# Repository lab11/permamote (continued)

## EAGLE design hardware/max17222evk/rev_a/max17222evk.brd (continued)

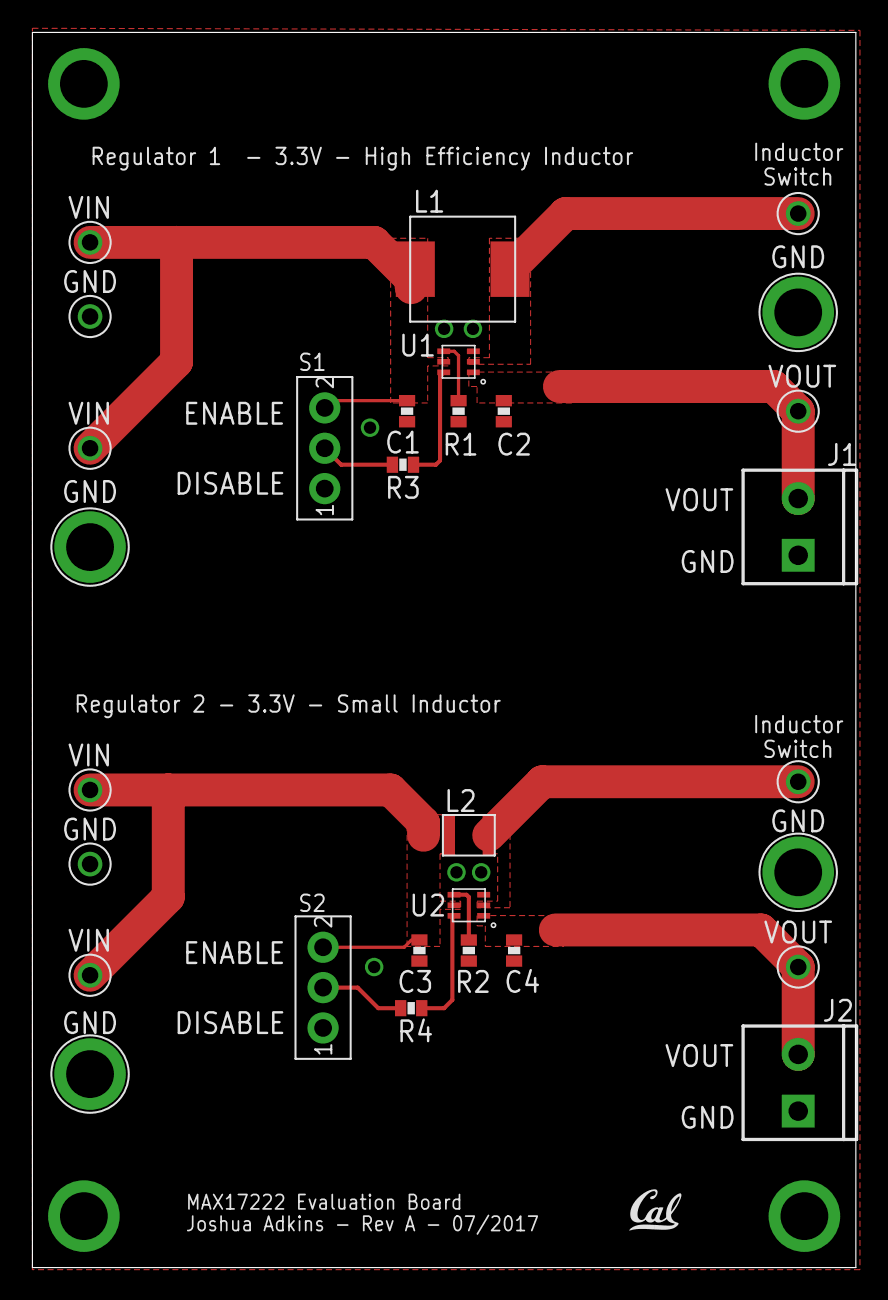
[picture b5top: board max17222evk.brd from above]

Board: 2 copper layers, 50.8 x 76.2 mm, 31 parts (0 on the bottom side), 13 nets.

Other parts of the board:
U$1: UCB_CAL_100MIL

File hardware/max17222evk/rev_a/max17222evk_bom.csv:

"Qty";"Value";"Device";"Package";"Parts";"Description";"DIGIKEY";"MANUFACTURER";"MANUFACTURER_PN";"NEWARK";
"2";"";"M023.5MM";"SCREWTERMINAL-3.5MM-2";"J1, J2";"Header 2";"277-1721-ND";"";"";"";
"4";"10uF";"CAPACITOR0603_CAP";"0603_CAP";"C1, C2, C3, C4";"SMD Capacitor";"490-3896-2-ND";"";"";"";
"1";"1uH";"INDUCTORDFE322512C";"DFE322512C";"L2";"A very specific inductor";"490-10590-1-ND";"";"";"";
"1";"1uH";"INDUCTORIHL2525CZ";"IHL-2525CZ";"L1";"A very specific inductor";"541-2562-1-ND";"";"";"";
"2";"33M";"RESISTOR0603_RES";"0603-RES";"R3, R4";"Resistor";"HMC0603JT33M0CT-ND";"";"";"";
"2";"80.6k";"RESISTOR0603_RES";"0603-RES";"R1, R2";"Resistor";"311-80.6KHRCT-ND";"";"";"";
"2";"MAX17222";"MAX17222";"UDFN-6-MAXIM";"U1, U2";"Very high efficiency, very low power boost converter suitable for EH applications";"MAX17222ELT+TCT-ND";"MAXIM INTEGRATED";"MAX17222ELT+T";"";
"10";"TEST_POINT_0.040IN";"TEST_POINT_0.040IN";"TESTPOINT_0.040IN";"TP3, TP4, TP5, TP6, TP7, TP8, TP9, TP10, TP13, TP14";"0.040in Test Point";"5001K-ND";"";"";"";
"4";"TEST_POINT_0.112IN";"TEST_POINT_0.112IN";"TESTPOINT_0.112IN";"TP1, TP2, TP11, TP12";"Solder terminal, turreted";"36-1519-2-ND";"";"";"40F6015";
"2";"TE_SSA12/SPDT";"TE_SSA12/SPDT";"TE_SSA12/SPDT";"S1, S2";"SWITCH SLIDE SPDT 2POS SSA SER";"450-1602-ND";"";"";"";

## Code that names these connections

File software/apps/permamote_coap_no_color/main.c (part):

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  NRF_LOG_INFO("Sensed voltage: vbat*100: %d, vsol*100: %d, vsec*100: %d", (int32_t)(vbat*100), (int32_t)(vsol*100), (int32_t)(vsec*100));

  // sense vbat_ok
  bool vbat_ok = nrf_gpio_pin_read(VBAT_OK);
  packet.data = (uint8_t*)&vbat_ok;
  packet.data_len = sizeof(vbat_ok);
  permamote_coap_send(&m_peer_address, "vbat_ok", false, &packet);
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}

static void pir_backoff_callback() {
  nrf_drv_gpiote_in_event_enable(PIR_OUT, 1);
}

static void pir_interrupt_callback(nrf_drv_gpiote_pin_t pin, nrf_gpiote_polarity_t action) {
  nrf_drv_gpiote_in_event_disable(PIR_OUT);
  uint32_t err_code = app_timer_start(pir_backoff, PIR_BACKOFF_PERIOD, NULL);
  APP_ERROR_CHECK(err_code);

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  nrf_gpio_cfg_output(TCS34725_EN);
  nrf_gpio_cfg_output(MS5637_EN);
  nrf_gpio_cfg_output(SI7021_EN);
  nrf_gpio_cfg_output(PIR_EN);
  nrf_gpio_pin_clear(MAX44009_EN);
  nrf_gpio_pin_clear(PIR_EN);
  nrf_gpio_pin_set(TCS34725_EN);
  nrf_gpio_pin_set(MS5637_EN);
  nrf_gpio_pin_set(SI7021_EN);
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  }
  nrf_drv_gpiote_in_config_t pir_gpio_config = GPIOTE_CONFIG_IN_SENSE_LOTOHI(1);
  pir_gpio_config.pull = NRF_GPIO_PIN_PULLDOWN;
  nrf_drv_gpiote_in_init(PIR_OUT, &pir_gpio_config, pir_interrupt_callback);
  nrf_drv_gpiote_in_event_enable(PIR_OUT, 1);

  // setup vbat sense
  nrf_gpio_cfg_input(VBAT_OK, NRF_GPIO_PIN_NOPULL);

  ab1815_init(&spi_instance);
  ab1815_control_t ab1815_config;
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
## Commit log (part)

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2018-07-19 coap is a better term
2018-07-19 coap app read id from flash
2018-07-20 add motion parsing
2018-07-23 add part marker to U12
2018-07-24 add PIR to coap app
2018-07-24 add parsing for temp/pressure
2018-07-24 Fixup si7021 driver to use twi mngr
    Add test app to print temp/humidity
2018-07-25 add humidity parsing
2018-07-25 Move jtag connector to back
2018-07-25 Add app support for humidity and voltage sensing
    fix humidity and light driver bugs
2018-07-25 update voltage names
2018-07-31 start driver for tcs34725
2018-08-02 add reset to parser
2018-08-02 better handling of corner cases, max44009
2018-08-02 Fill out tcs driver
2018-08-07 Add driver and test app for RTC
    test app sets rtc time, prints out read time every 5 seconds
2018-08-08 Add function to convert unix to ab1815 time format
2018-08-27 Add new pin defs for revb
2018-08-28 Attempt to add ntp+rtc support to permamote
    SPI manager sucks and hangs - need to use drv interface
2018-08-28 start of test app for tcs
2018-08-29 TCS driver and test working
2018-09-05 Switch to new NRFX base build system
    Add permamote board config files
    All test apps working on new build system - print over rtt
2018-09-05 Redesign case
    unibody design with clips to hold solar panel above board
2018-09-10 fix led count
2018-09-10 Use permamote packet send layer
2018-09-11 add light color measurements to main app
2018-09-11 update README to be more informative
2018-09-14 add debug print/sending for buffer allocation
2018-09-24 add topic to parsed message
2018-10-03 use channel 25 for less interference
2018-10-04 add support for rtc alarm
    Use alarm in coap app to periodically update rtc with ntp
2018-10-04 start state machine
2018-10-04 fix up ntp error handling - handle timeout
    fix rtc alarm repeat time setting
2018-10-05 add simple software watchdog
2018-10-06 out for quotes
2018-10-08 Add rtc watchdog
    coap app now enables and tickles watchdog upon successful packet queue
    and if connected to network
2018-10-11 Move lighting control stuff to own repo
2018-10-28 add light sensing to periodic
2018-11-28 actually turn off PIR
    add intents for buffer
2018-12-05 parse vbat_ok
2018-12-08 Add autoranging of color sensor
    Autorange based on clear channel count, 4 settings.
    Also change method for calculating color temperature
2018-12-11 use dns to resolve coap/ntp addresses
2018-12-14 Update to new openthread libraries, nrf sdk 15.2.0
    Update coap app to only tickle watchdog periodically instead of every
    send.
2019-01-07 Add a background bootloader for thread dfu
    Add bootloader board files
2019-01-08 relax sensor modes
2019-01-10 Got DFU over thread working
    Currently need to manually follow steps for generating/merging
    bootloader settings as listed here: https://www.nordicsemi.com/DocLib/Content/SDK_Doc/Thread_SDK/v2-0-0/thread_example_dfu
    Need to play around with block sizes and polling intervals for faster
    DFU, but it works!
2019-01-12 Add connect and address resolve to state machine
2019-01-14 differentiate sensing periods
2019-01-16 deprecate color sensor
2019-01-24 start icount calibration script
2019-01-29 switch to yaml config
2019-02-04 Turn LED on in main
2019-02-07 start script to process
2019-02-08 clean up curve
2019-02-08 try 4 wire sensing, plot data
2019-02-12 clean up processing
2019-02-12 percent to capacity
2019-02-12 manually set to 0 current instead of high z
2019-02-13 add hyst lines
2019-02-16 Stored a variable in flash
2019-02-20 Continue testing with flash storage API
2019-02-21 More flash API work
2019-02-22 Refactor address resolution and NTP update
    Add several more states to handle NTP updates, polling frequency updates
2019-02-23 Fix double counted PIR events
    Check dns errors, wait until successful
2019-02-23 Change discovery to periodic loop
2019-02-25 fix rev number in sch
2019-02-26 More fstorage disappointment
2019-03-05 Refactor simulator into class
    Clean up simulator, switch to yaml config
2019-03-05 Recalibrating fstorage stuff to deal with the fact that NVMC can't write 2x to same addr
2019-03-07 Add tutorial
2019-03-07 Create new test app for flash variables, using FDS
2019-03-07 Perform first FDS write
2019-03-08 debugging info - undo a lot of this later
2019-03-08 correctly sign firwmare
2019-03-11 Update openthread libs for SNTP
2019-03-12 Create FDS write wrapper function, start work on FDS read wrapper function
2019-03-13 add weight to parse js
2019-03-13 add permamote scale code
2019-03-14 Create more FDS helper functions
2019-03-18 Fix url in config, logic in address resolution
2019-03-18 Start new header file
2019-03-22 Work on bootstrapping problem for flash variable names
2019-03-22 Refactoring to implement tag-struct strategy
2019-03-25 Add app-level timeout for DFU failure
    Also now check for updates every day (24 hours)
2019-03-30 remove public keys
2019-03-30 Use actual update server
2019-03-30 Better performance with different coap settings
    Still need to figure out why no retransmit on dfu side
2019-03-31 pull up nrf5x-base
2019-03-31 print out git version
2019-04-02 Only start coap tick timer when performing dfu
    Also disable monitor for hung dfu
2019-04-02 add version string packet on start
2019-04-02 this repo is almost always dirty
2019-04-02 print out git version on build
2019-04-03 continue work
2019-04-04 refactor flash variable init
2019-04-11 split flash storage functions by data type
2019-04-12 fix bugs with float storage and update; still have to fix bugs with string update
2019-04-23 Create separate branch for non-volatile parameter updates
2019-04-23 Continue testing string updates with flash storage
2019-04-24 update readme to fix broken links
2019-04-26 Fix broken readme link
2019-04-26 Store Device ID in last bit of flash
    Should fix #6
    Move bootloader back, page for Device ID
2019-04-29 include more reserved pages
2019-04-30 Clean up garbage files, keys
2019-04-30 Don't need bootloader for this example
    Fix naming conflict in nrf52832
2019-04-30 Clean up flash test
2019-04-30 move flash storage to common folder
2019-05-02 Use new flash storage lib to store ID
2019-05-03 ensure dfu does not overwrite app data
2019-05-03 add jitter to dfu update
2019-05-09 Reduce frequency of adc measurements
    Make interrupt-based measurements confirmable
2019-05-10 refactor state machine
2019-05-17 send discover on boot
2019-06-05 reduce light sensor sensitivity
2019-06-05 Was not preserving openthread flash pages
    Set reserved pages to 4, ensure DFU and FDS account for them
2019-07-07 Add watchdog back in because can't fix dfu bug
2019-07-07 don't stop coap timer tick
2019-07-08 at a minimum, sample light sensor every so often
2019-07-09 Commit rev d
    Only major change is moving button + led. Button was previously
    partially overlapping battery connection
2019-07-17 clean and orient design blocks
2019-07-17 Route signals on board - no airwires or major drc
    Need to add optional MSP430
2019-07-30 Don't need `make flash_first_dfu` anymore!
2019-07-31 Move to new nRF52x-base repo
    [nRF52x](https://github.com/lab11/nrf52x-base)
2019-09-14 fix missing nrf52x commit
2019-09-14 Update README for git lfs
2019-09-19 Start ADC test
    got down to 400uA for two channels
2019-09-20 ADC sampling works with PPI
    but draws considerable current
2019-10-02 bump nrf52x
2019-10-04 Update Permamote to periodically send thread info
2019-10-14 Use nanopb instead of protobuf-c
    Update nordic's use of nanopb and patch implementation
    Update permamote app to use protobuf
    Need to fix cloud infrastructure to support protobufs
    Need to figure out platform/version independent way of generating proto
    c code
2019-10-23 fix exti floating
2019-10-23 Fix exti in rev d
2019-10-24 Add decoupling cap for camera supply
2019-10-25 Better support for protobuf generation
2019-10-26 add my comments
2019-10-26 oops missed the LED
2019-10-30 Incorporate branden's suggestions
    Add power switch, need to layout
2019-11-02 Route power switch
2019-11-02 ran the script and requested quote
2019-11-04 Holes for 18mm holders
2019-11-07 Fix BOM errors for resistor + battery
2019-11-07 flatten protobuf structure
2019-11-16 add proto files for testing
2019-11-16 rename to match old names of fields
2019-11-18 Benchmark CLA/CS measurements
2019-11-19 made revisions from schematic review
2019-11-20 added sd card
2019-11-26 Implement MCLK and some of SPIS
2019-11-26 Get 8MHz clock working
2019-11-27 freaking idiot
2019-11-28 rebuffer SPI for continuous
2019-12-01 Implement blocking image capture
2019-12-02 Got full frame color images working
2019-12-07 layout
2019-12-12 It sleeps!
2020-01-01 routed everything except confused about ground and vcc
2020-01-07 more routing fixes
2020-01-09 clean up himax driver, add more comments
2020-01-10 made more changes but still having TPD3F303DPVR polygon issues
2020-01-18 Jesus christ neal can you read
2020-01-21 add sleep example app
2020-01-22 Add coap + camera application, working together
    Needed to change timer used for camera, as openthread used same timer.
    Fix up interface to camera a little so remains low power - still not
    quite where I want it
2020-01-31 before moving u10
2020-01-31 more board fixes
2020-02-10 Fix some initialization errors for camera api
2020-02-13 got rid of erc errors
2020-02-15 cleaned up wirestubs
2020-02-18 taking pictures + ntp + dns
2020-02-20 Properly manage poll period for image sending
2020-02-23 Add image_raw field to proto
2020-02-23 Make `permamote_coap` a library file
2020-02-23 Permacam send discovery + version
2020-02-24 Enable device ID
2020-02-26 Add updating etag + update block callback
2020-02-27 update 9160
2020-03-02 Add jpeg encoding library, add to test app
2020-03-04 add resize to camera test
2020-03-07 add jpeg field
2020-03-07 Send jpeg instead of raw
2020-03-08 Fix memory interface bugs with jpec+interrupt init
2020-03-17 add jpeg quality to parse
2020-03-23 minor stuff
2020-03-24 Move to more generic gateway_coap layer
2020-03-25 rename
2020-03-26 add light/pir back in
2020-03-28 Add timeout for autoexposure wait
2020-03-30 Add app layer abstraction for block send
2020-03-31 Add exposure + image id fields
2020-04-01 add travis
2020-04-05 bring nrf52x-base up to master
2020-04-05 Fix up a bunch of apps
2020-04-05 get rid of merghex dependency
2020-04-13 fix build for do nothing
2020-04-13 add travis for permacam
2020-04-28 add flag to use gateway code
2020-04-28 a temporary branch that points to an nrf5x-base PR
2020-05-07 Update build system - merge all *.hex together
2020-05-07 Update documentation for building - no lfs/copy keys
2020-05-11 Add image processing applications
    For demosaicing and performing yolov3 object detection
2020-05-13 Add application for testing different jpeg quality
    Also add start of scripts to collect images and process them
2020-05-15 Remove parsing requirements from test app
2020-05-15 mpn and digikey
2020-05-15 pull nrf52x-base up to master
2020-05-15 Add plotting for size + time, detections
2020-05-15 removed lte antenna from bom
2020-05-18 outline, label fixes
2020-05-20 pins overlapping cage need to fix
2020-05-20 holes arent covered anymore
2020-05-20 remove tp and jlink from bom
2020-06-03 disable send light, add voltage
2020-06-03 Fix board files to support new sdk
2020-06-28 nrfx_nvmc is sdk 16 only
2020-07-07 rehaul simulator + sweep, add permacam configs
2020-07-07 to pandas df
2020-07-07 don't make huge lists
2020-07-08 add number of events
2020-07-17 add last few config changes
2020-07-17 Add options for quality or periodic for camera apps
2020-07-17 Fix flash storage array bug, fix typo in camera script
2020-08-10 up nrf5x-base for erase
2020-08-11 Alter state machine to order address resolve + ntp
    First resolve addresses, then try to get time. Also add reboot if
    offline for a day.
2020-08-15 Up nrf52x-base
2020-08-15 fix inverted logic causing long poll period
2020-08-16 Clear resolve fail on success
2020-10-08 add service for demosaicing images
2020-10-10 set up detection as service
2021-11-09 Add i2c peripheral for receiving jpegs over i2c
2021-11-10 try to use SPI
2022-04-04 add updated sweep/simulate
2022-04-04 add requirements.txt
2022-11-18 add synth setup d outdoor trace
